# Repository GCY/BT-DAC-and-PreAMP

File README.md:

# BT-DAC-and-PreAMP
CSR64215 + PCM5102 + PreAMP(Dual OPA227)

SW4 = Play/Stop </br>
SW3 = Vol+ </br>
SW2 = Vol- </br>
SW1 = On/Off </br>

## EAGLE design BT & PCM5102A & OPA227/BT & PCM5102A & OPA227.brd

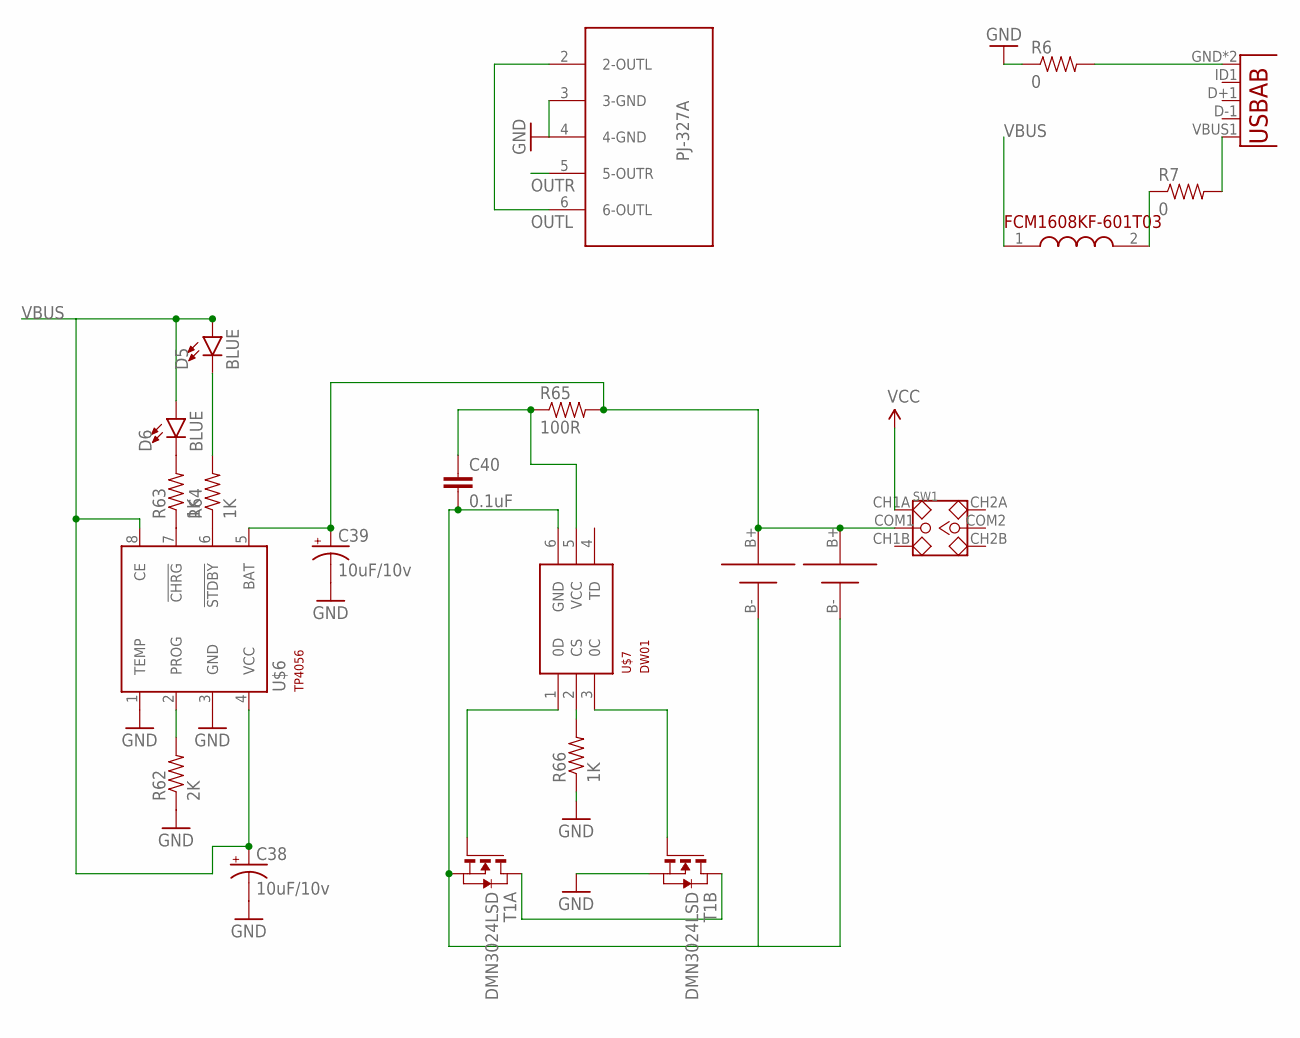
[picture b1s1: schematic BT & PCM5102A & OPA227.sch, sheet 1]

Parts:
C38, C39: 10uF/10v; EIA3216-KIT
C40: 0.1uF; 0603-CAP
D5, D6: BLUE; LED-0603
R6, R7: 0; 0805
R62: 2K; 0603-RES
R63, R64, R66: 1K; 0603-RES
R65: 100R; 0603-RES
SW1: SMD-TOGGLE-SWITCH-2CH(2X3P-7X3.5MM); SW6-2.54-SMD-7.0X3.5X1.5MM
T1: DMN3024LSD; TSSOP-8
U1: USB""; USB-MICRO-SMD
U$2: PJ-327A
U$4: FCM1608KF-601T03
U$5, U$8: 18650SMD
U$6: TP4056; SOT23-8
U$7: DW01; SOT23-6

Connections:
GND: C38.C (-), C39.C (-), R6.1, R62.1, R66.1, T1.6 (S), T1.7 (S), U$2.3 (3-GND), U$2.4 (4-GND), U$6.1 (TEMP), U$6.3 (GND); also elsewhere on the board
unnamed: R7.2, U1.VBUS1 (VBUS)
unnamed: C39.A (+), R65.2, SW1.COM1, U$5.B+, U$6.5 (BAT), U$8.B+
unnamed: R7.1, U$4.2 (2.OUT)
unnamed: R6.2, U1.GND, U1.GND1 (GND)
unnamed: R62.2, U$6.2 (PROG)
unnamed: R63.1, U$6.7 (!CHRG)
unnamed: R64.1, U$6.6 (!STDBY)
unnamed: D6.C, R63.2
unnamed: D5.C, R64.2
unnamed: C40.1, R65.1, U$7.5 (VCC)
unnamed: C40.2, T1.2 (S), T1.3 (S), U$5.B-, U$7.6 (GND), U$8.B-
unnamed: T1.4 (G), U$7.1 (0D)
unnamed: R66.2, U$7.2 (CS)
unnamed: T1.1 (D), T1.8 (D)
unnamed: T1.5 (G), U$7.3 (0C)
OUTL: U$2.2 (2-OUTL), U$2.6 (6-OUTL); also elsewhere on the board
OUTR: U$2.5 (5-OUTR); also elsewhere on the board
VBUS: C38.A (+), D5.A, D6.A, U$4.1 (1.IN), U$6.4 (VCC), U$6.8 (CE)
VCC: SW1.CH1A; also elsewhere on the board

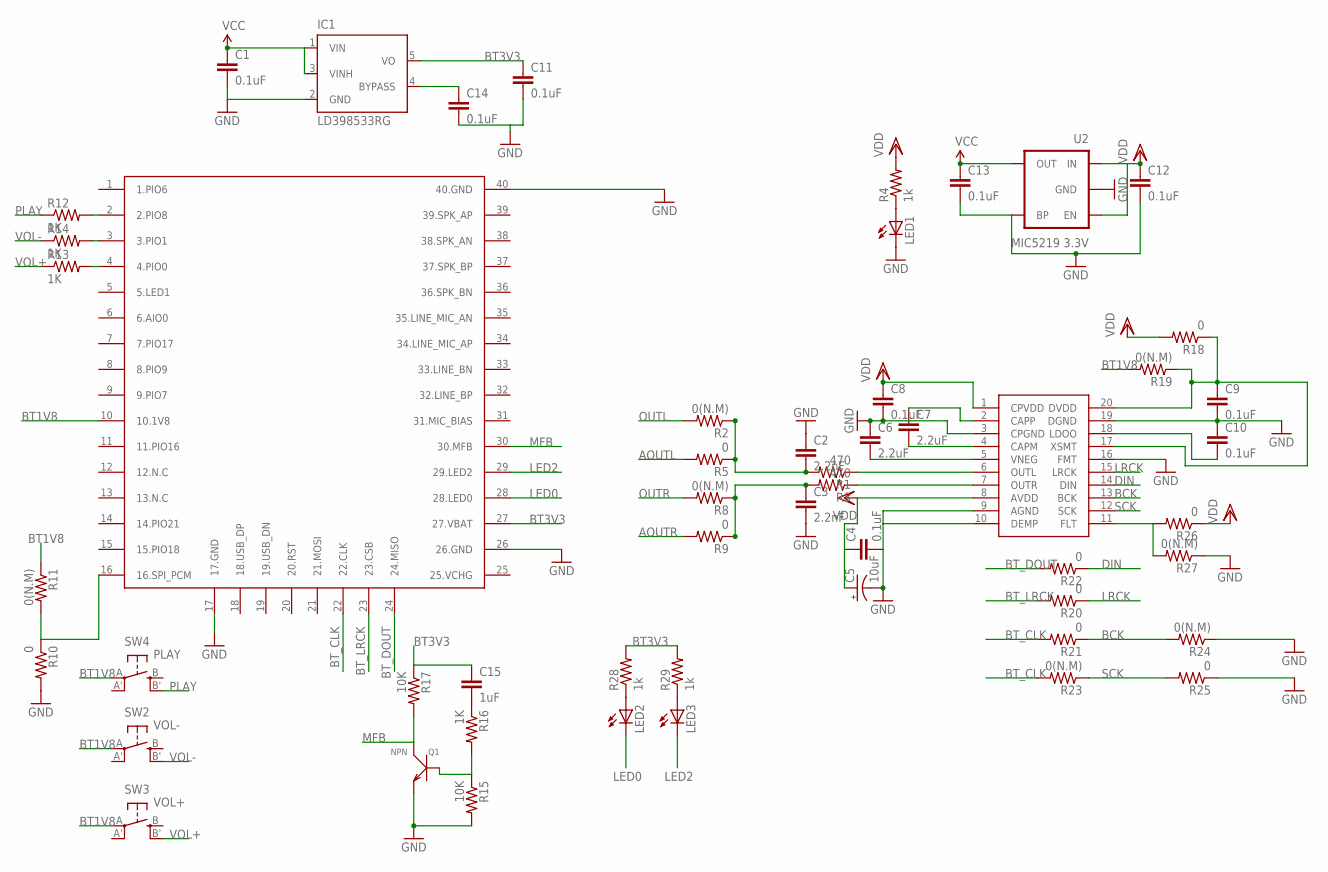
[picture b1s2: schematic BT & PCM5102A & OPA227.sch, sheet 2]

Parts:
C1, C4, C8, C9, C10, C11, C12, C13, C14: 0.1uF; 1206
C2, C3: 2.2nF; C5B2.5
C5: 10uF; NIPPON_F80
C6, C7: 2.2uF; 1206
C15: 1uF; C5B2.5
IC1: LD398533RG; TSOT23-5L
LED1, LED2, LED3: LEDCHIP-LED0805; CHIP-LED0805
Q1: NPN; SOT-23
R1, R3: 470; 1206
R2, R8, R11, R19, R23, R24, R27: 0(N.M); 1206
R4, R28, R29: 1k; 1206
R5, R9, R10, R18, R20, R21, R22, R25, R26: 0; 1206
R12, R13, R14, R16: 1K; 1206
R15, R17: 10K; 1206
SW2: VOL-; EVQ-Q2
SW3: VOL+; EVQ-Q2
SW4: PLAY; EVQ-Q2
U2: MIC5219 3.3V; SOT23-5
U$1: PCM5102; TSSOP20
U$3: BTM625

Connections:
AOUTL: R5.2; also elsewhere on the board
AOUTR: R9.2; also elsewhere on the board
BCK: R21.1, R24.2, U$1.13 (BCK)
BT1V8: R11.1, R19.2, SW2.A, SW3.A, SW4.A, U$3.10 (10.1V8)
BT3V3: C11.1, C15.1, IC1.5 (VO), R17.1, R28.2, R29.2, U$3.27 (27.VBAT)
BT_CLK: R21.2, R23.2, U$3.22 (22.CLK)
BT_DOUT: R22.2, U$3.24 (24.MISO)
BT_LRCK: R20.2, U$3.23 (23.CSB)
DIN: R22.1, U$1.14 (DIN)
GND: C1.2, C2.1, C3.2, C4.2, C5.-, C6.1, C8.2, C9.2, C10.1, C11.2, C12.2, C13.2, C14.2, IC1.2 (GND), LED1.C, Q1.2 (E), R10.2, R15.2, R24.1, R25.1, R27.1, U2.2 (GND), U2.4 (BP), U$1.3 (CPGND), U$1.9 (AGND), U$1.10 (DEMP), U$1.16 (FMT), U$1.19 (DGND), U$3.17 (17.GND), U$3.26 (26.GND), U$3.40 (40.GND); also elsewhere on the board
LED0: LED2.C, U$3.28 (28.LED0)
LED2: LED3.C, U$3.29 (29.LED2)
LRCK: R20.1, U$1.15 (LRCK)
MFB: Q1.3 (C), R17.2, U$3.30 (30.MFB)
unnamed: C7.1, U$1.2 (CAPP)
unnamed: LED1.A, R4.1
unnamed: C14.1, IC1.4 (BYPASS)
unnamed: C7.2, U$1.4 (CAPM)
unnamed: R3.1, U$1.7 (OUTR)
unnamed: R1.1, U$1.6 (OUTL)
unnamed: C6.2, U$1.5 (VNEG)
unnamed: C10.2, U$1.18 (LDOO)
unnamed: R12.2, U$3.2 (2.PIO8)
unnamed: C15.2, R16.1
unnamed: R14.2, U$3.3 (3.PIO1)
unnamed: R10.1, R11.2, U$3.16 (16.SPI_PCM)
unnamed: Q1.1 (B), R15.1, R16.2
unnamed: C9.1, R18.1, R19.1, U$1.17 (XSMT), U$1.20 (DVDD)
unnamed: R26.2, R27.2, U$1.11 (FLT)
unnamed: R13.2, U$3.4 (4.PIO0)
unnamed: LED2.A, R28.1
unnamed: LED3.A, R29.1
OUTL: C2.2, R1.2, R2.1, R2.2, R5.1; also elsewhere on the board
OUTR: C3.1, R3.2, R8.1, R8.2, R9.1; also elsewhere on the board
PLAY: R12.1, SW4.B' (S1)
SCK: R23.1, R25.2, U$1.12 (SCK)
VCC: C1.1, C13.1, IC1.1 (VIN), IC1.3 (VINH), U2.5 (OUT); also elsewhere on the board
VDD: C4.1, C5.+, C8.1, C12.1, R4.2, R18.2, R26.1, U2.1 (IN), U2.3 (EN), U$1.1 (CPVDD), U$1.8 (AVDD)
VOL+: R13.1, SW3.B' (S1)
VOL-: R14.1, SW2.B' (S1)

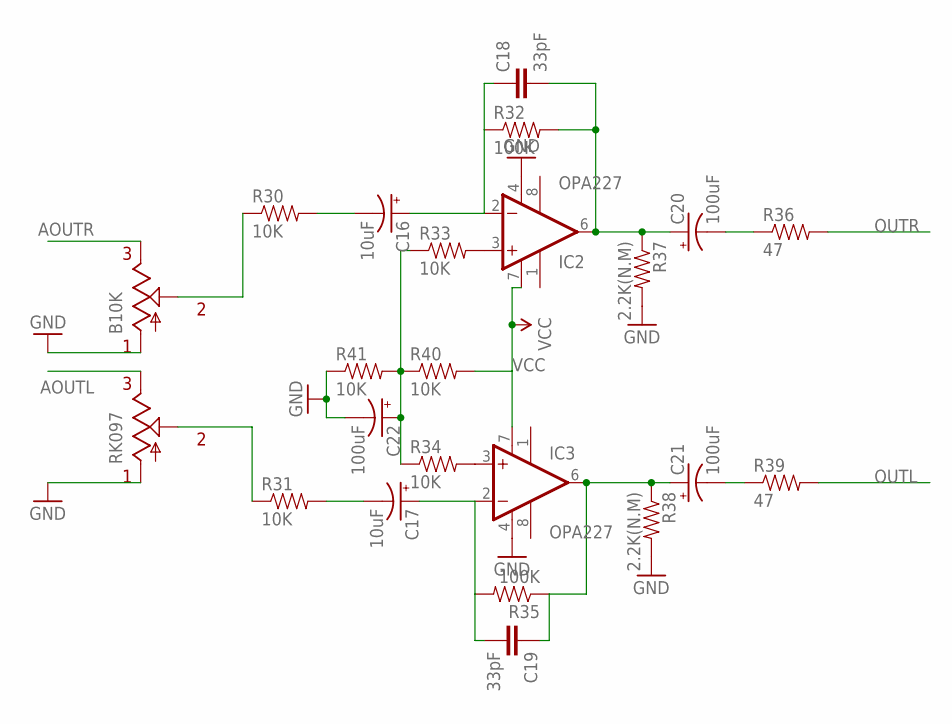
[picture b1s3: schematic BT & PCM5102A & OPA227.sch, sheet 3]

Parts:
C16, C17: 10uF; CPOL-RADIAL-2.5MM-5MM-KIT
C18, C19: 33pF; 0603
C20, C21, C22: 100uF; CPOL-RADIAL-2.5MM-5MM-KIT
IC2, IC3: OPA227; SO08
R30, R31, R33, R34, R40, R41: 10K; 1206
R32, R35: 100K; 1206
R36, R39: 47; 1206
R37, R38: 2.2K(N.M); 1206
RK097: B10K; RK097-DUAL-ELEMENT

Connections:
AOUTL: RK097.P$6 (E1); also elsewhere on the board
AOUTR: RK097.P$1 (E); also elsewhere on the board
GND: C22.2 (-), IC2.4 (V-), IC3.4 (V-), R37.2, R38.2, R41.1, RK097.P$3 (A), RK097.P$4 (A1); also elsewhere on the board
unnamed: C16.1 (+), C18.1, IC2.2 (-IN), R32.1
unnamed: C16.2 (-), R30.2
unnamed: C17.1 (+), C19.2, IC3.2 (-IN), R35.2
unnamed: C17.2 (-), R31.2
unnamed: C18.2, C20.1 (+), IC2.6 (OUT), R32.2, R37.1
unnamed: C20.2 (-), R36.1
unnamed: C19.1, C21.1 (+), IC3.6 (OUT), R35.1, R38.1
unnamed: C21.2 (-), R39.1
unnamed: IC3.3 (+IN), R34.2
unnamed: IC2.3 (+IN), R33.2
unnamed: C22.1 (+), R33.1, R34.1, R40.1, R41.2
unnamed: R31.1, RK097.P$5 (S1)
unnamed: R30.1, RK097.P$2 (S)
OUTL: R39.2; also elsewhere on the board
OUTR: R36.2; also elsewhere on the board
VCC: IC2.7 (V+), IC3.7 (V+), R40.2; also elsewhere on the board

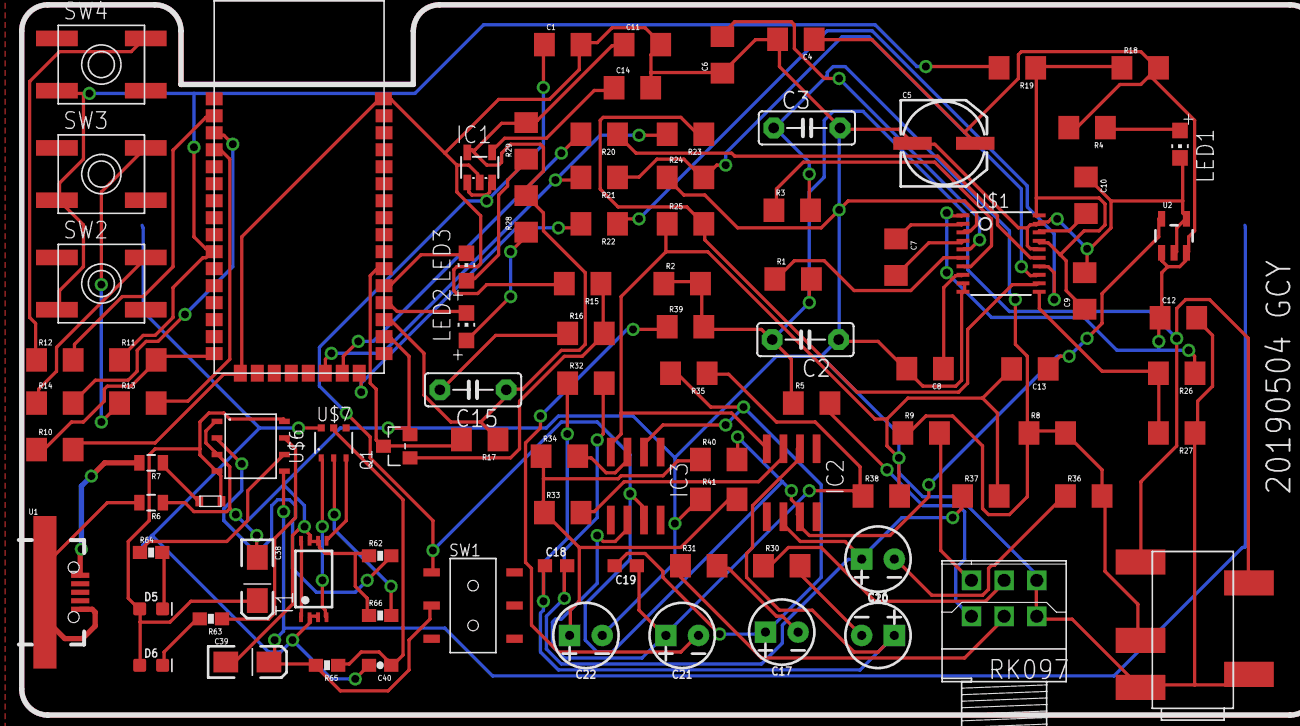
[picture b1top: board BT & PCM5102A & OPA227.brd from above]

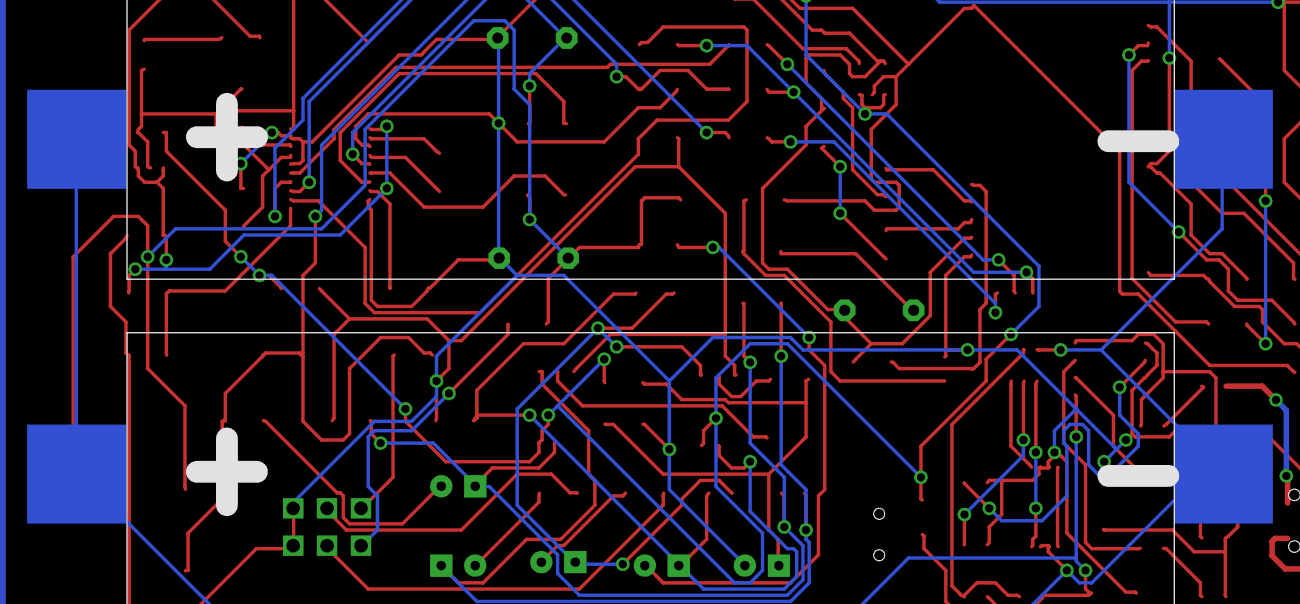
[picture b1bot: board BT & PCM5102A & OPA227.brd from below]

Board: 2 copper layers, 96 parts (2 on the bottom side), 69 nets.

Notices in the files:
parts and their libraries:
SparkFun-PowerIC: Licensing: CC v3.0 Share-Alike You are welcome to use this library for commercial purposes.
